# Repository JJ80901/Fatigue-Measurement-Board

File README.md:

# Fatigue-Measurement-Board
**Precision Displacement Sensing**

This board is designed to process and digitize a ±10V analog signal from a laser displacement sensor, ensuring high-fidelity data acquisition for fatigue testing applications. 

The signal enters through a BNC connector, passes through ESD protection and an RF filter, and is then scaled down to a ±1.65V range using a resistor divider. A non-inverting summing amplifier shifts the signal into a 0-3.3V range, with a 1.65V bias generated by an op-amp follower from a half-resistor divider off the 3.3V power rail.

To prevent aliasing, the conditioned signal passes through a third-order Butterworth Sallen-Key low-pass filter with a 5kHz cutoff frequency, optimized for sampling rates up to 1kHz. The filtered signal is digitized by an ADC141S626 14-bit ADC, which interfaces over SPI with an STM32F103CBT6 microcontroller, responsible for managing data acquisition and transmission.

Power is regulated using a TLV62569 switching regulator for 3.3V conversion and an HT7533-1 LDO, ensuring clean and stable power for the analog front end and microcontroller. 

This design improves upon earlier iterations by incorporating better filtering, precise voltage scaling, and a high-resolution ADC, making it ideal for fatigue analysis, precision displacement measurement, and other high-accuracy signal acquisition applications.

---

### What you'll find in this repository:
- Hardware designs (made in KiCad)
- STM32 Application Notes
- Device datasheets
- Circuit simulations

---

### Repository Project Structure:
- *3D Models* - Models for PCB components not found in the standard KiCad library
- *BOM* - An interactive HTML bill of materials (generated from the *Interactive HTML BOM* Plugin)
- *Datasheets* - Datasheets for specific devices used, such as the buck converter, LDO, Op-Amp, etc.
- *Docs* - STM32 application notes for crystal and USB design
- *Fatigue Test Board* - KiCad design files
- *Images* - High quality renderings of the final PCB in 3D
- *Libraries* - Folders to include schematic symbols and footprints for components not found in the standard KiCad library
- *Outputs* - Gerber files for manufacturing the PCB
- *Schematics* - PDFs of entire PCB schematic
- *Simulations* - LTSpice simulation block with any custom component libraries

---
***Disclaimer**: This board is ordered, but not yet tested!*

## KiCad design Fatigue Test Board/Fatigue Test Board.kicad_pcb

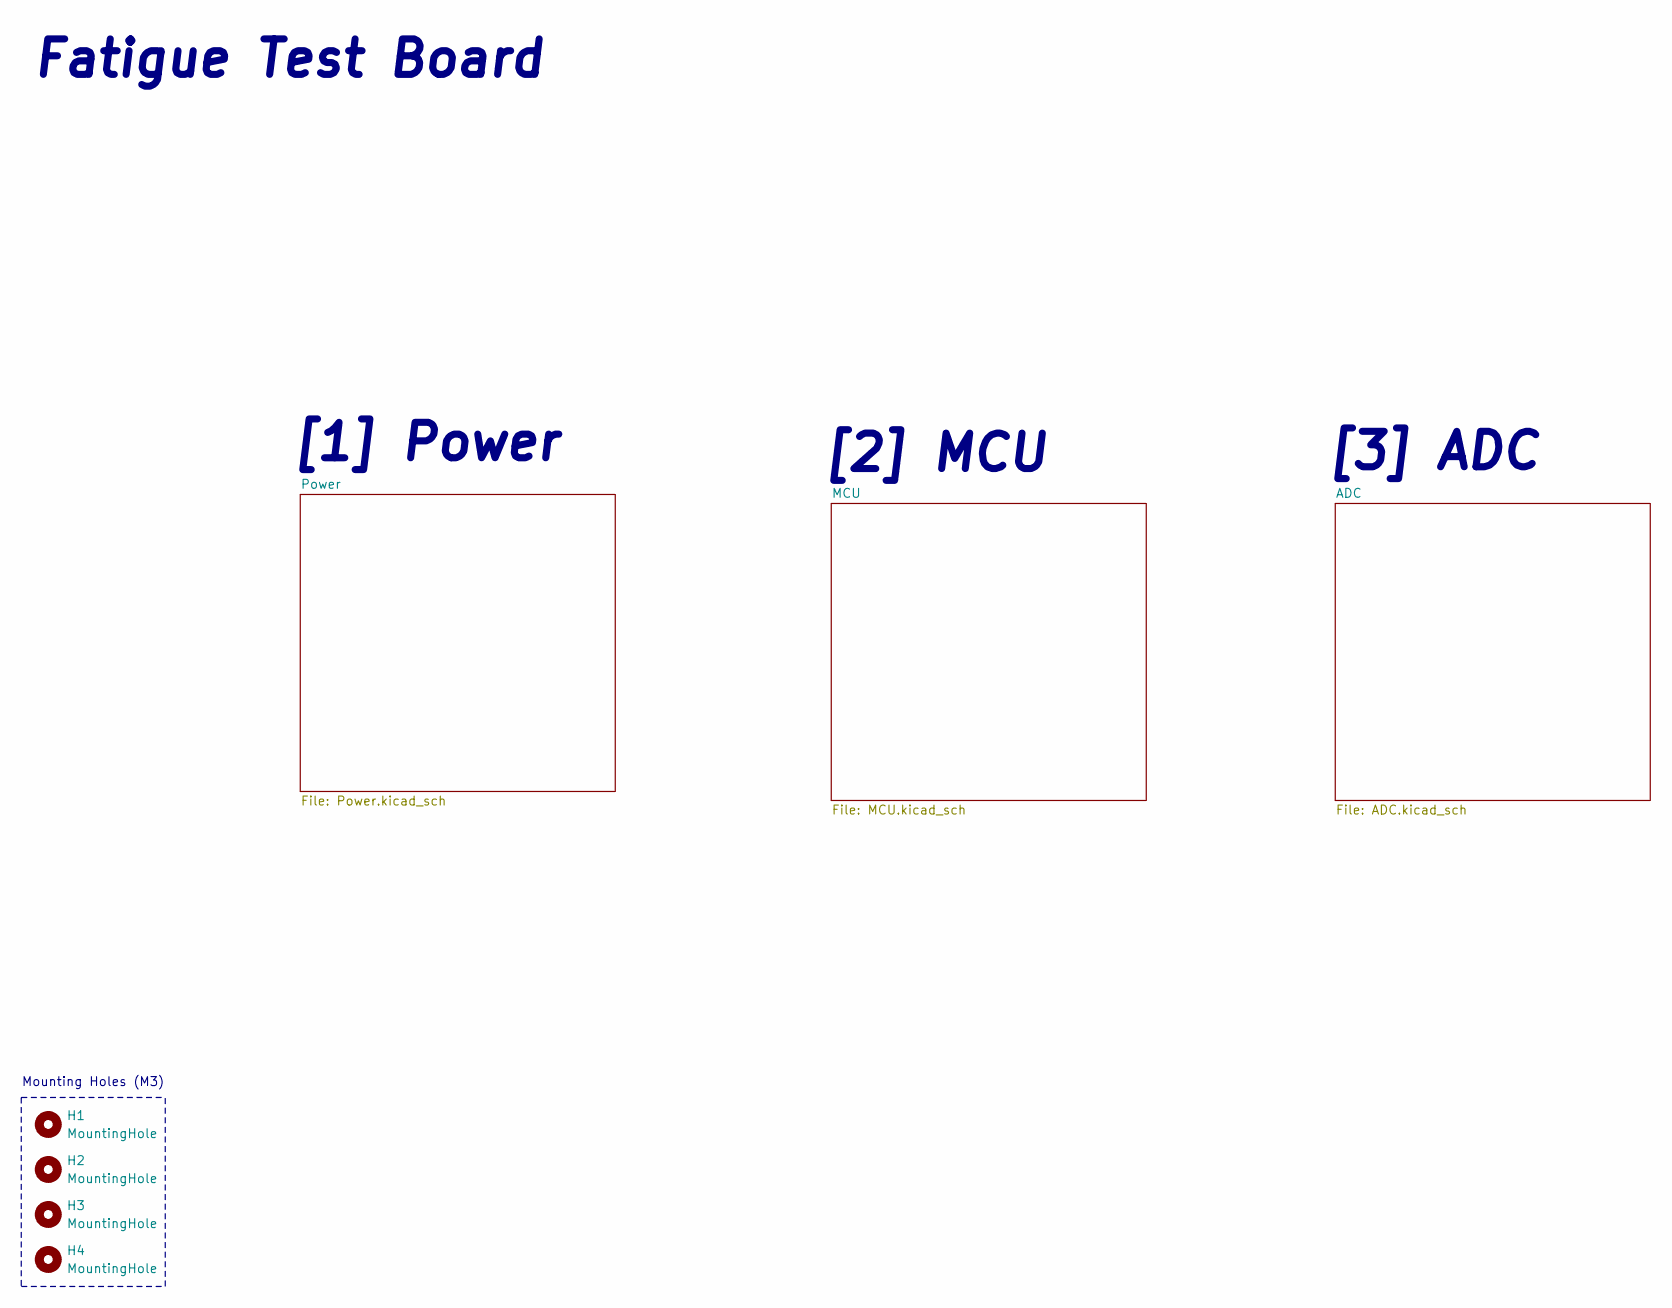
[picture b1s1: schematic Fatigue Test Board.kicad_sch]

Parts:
H1, H2, H3, H4: MountingHole; MountingHole_3.2mm_M3

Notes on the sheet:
[2] MCU
[3] ADC
Fatigue Test Board
[1] Power
Mounting Holes (M3)

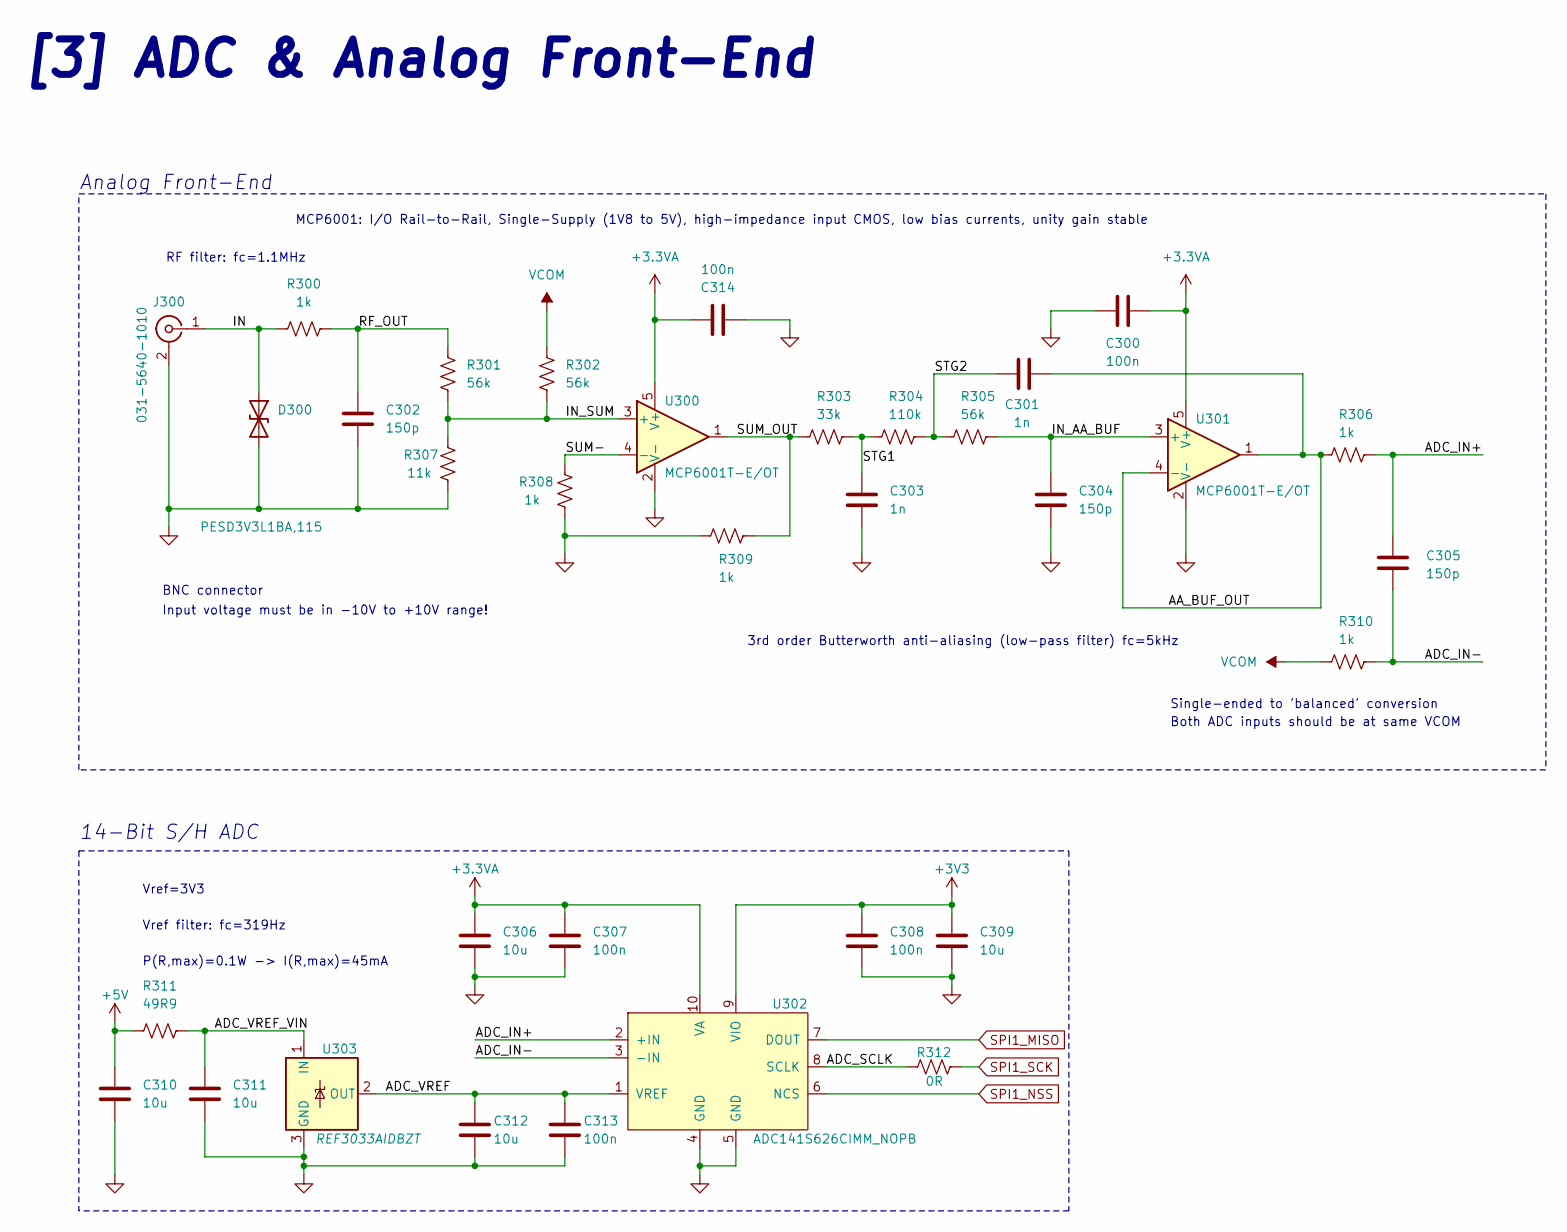
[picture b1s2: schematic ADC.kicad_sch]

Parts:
C300, C307, C308, C313, C314: 100n; C_0603_1608Metric_Pad1.08x0.95mm_HandSolder
C301, C303: 1n; C_0402_1005Metric_Pad0.74x0.62mm_HandSolder
C302, C304, C305: 150p; C_0402_1005Metric_Pad0.74x0.62mm_HandSolder
C306, C309, C310, C311, C312: 10u; C_0603_1608Metric_Pad1.08x0.95mm_HandSolder
D300: PESD3V3L1BA,115; D_SOD-323
J300: 031-5640-1010; CONN_73138-5033_MOL
R300, R306, R308, R309, R310: 1k; R_0603_1608Metric_Pad0.98x0.95mm_HandSolder
R301, R302, R305: 56k; R_0603_1608Metric_Pad0.98x0.95mm_HandSolder
R303: 33k; R_0603_1608Metric_Pad0.98x0.95mm_HandSolder
R304: 110k; R_0603_1608Metric_Pad0.98x0.95mm_HandSolder
R307: 11k; R_0603_1608Metric_Pad0.98x0.95mm_HandSolder
R311: 49R9; R_0603_1608Metric_Pad0.98x0.95mm_HandSolder
R312: 0R; R_0603_1608Metric_Pad0.98x0.95mm_HandSolder
U300, U301: MCP6001T-E/OT; SOT-23-5
U302: ADC141S626CIMM_NOPB; SOP50P490X110-10N
U303: REF3033AIDBZT; SOT-23

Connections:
+3.3VA: C300.1, C306.1, C307.1, C314.1, U300.5 (V+), U301.5 (V+), U302.10 (VA); also elsewhere on the board
+3V3: C308.1, C309.1, U302.9 (VIO); also elsewhere on the board
+5V: C310.1, R311.1; also elsewhere on the board
/ADC/AA_BUF_OUT: C301.2, R306.2, U301.1, U301.4 (-)
/ADC/ADC_IN+: C305.1, R306.1, U302.2 (+IN)
/ADC/ADC_IN-: C305.2, R310.1, U302.3 (-IN)
/ADC/ADC_SCLK: R312.2, U302.8 (SCLK)
/ADC/ADC_VREF: C312.1, C313.1, U302.1 (VREF), U303.2 (OUT)
/ADC/ADC_VREF_VIN: C311.1, R311.2, U303.1 (IN)
/ADC/IN: D300.1 (A1), J300.1 (In), R300.1
/ADC/IN_AA_BUF: C304.1, R305.1, U301.3 (+)
/ADC/IN_SUM: R301.2, R302.2, R307.1, U300.3 (+)
/ADC/RF_OUT: C302.1, R300.2, R301.1
/ADC/STG1: C303.1, R303.1, R304.2
/ADC/STG2: C301.1, R304.1, R305.2
/ADC/SUM-: R308.1, U300.4 (-)
/ADC/SUM_OUT: R303.2, R309.1, U300.1
GND: C300.2, C302.2, C303.2, C304.2, C306.2, C307.2, C308.2, C309.2, C310.2, C311.2, C312.2, C313.2, C314.2, D300.2 (A2), J300.2 (Ext), R307.2, R308.2, R309.2, U300.2 (V-), U301.2 (V-), U302.4 (GND), U302.5 (GND), U303.3 (GND); also elsewhere on the board
SPI1_MISO: U302.7 (DOUT); also elsewhere on the board
SPI1_NSS: U302.6 (NCS); also elsewhere on the board
SPI1_SCK: R312.1; also elsewhere on the board
VCOM: R302.1, R310.2; also elsewhere on the board

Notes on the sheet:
[3] ADC & Analog Front-End
RF filter: fc=1.1MHz
MCP6001: I/O Rail-to-Rail, Single-Supply (1V8 to 5V), high-impedance input CMOS, low bias currents, unity gain stable
3rd order Butterworth anti-aliasing (low-pass filter) fc=5kHz
P(R,max)=0.1W -> I(R,max)=45mA
Input voltage must be in -10V to +10V range!
Vref=3V3
Single-ended to 'balanced' conversion
Analog Front-End
Both ADC inputs should be at same VCOM
BNC connector
Vref filter: fc=319Hz
14-Bit S/H ADC

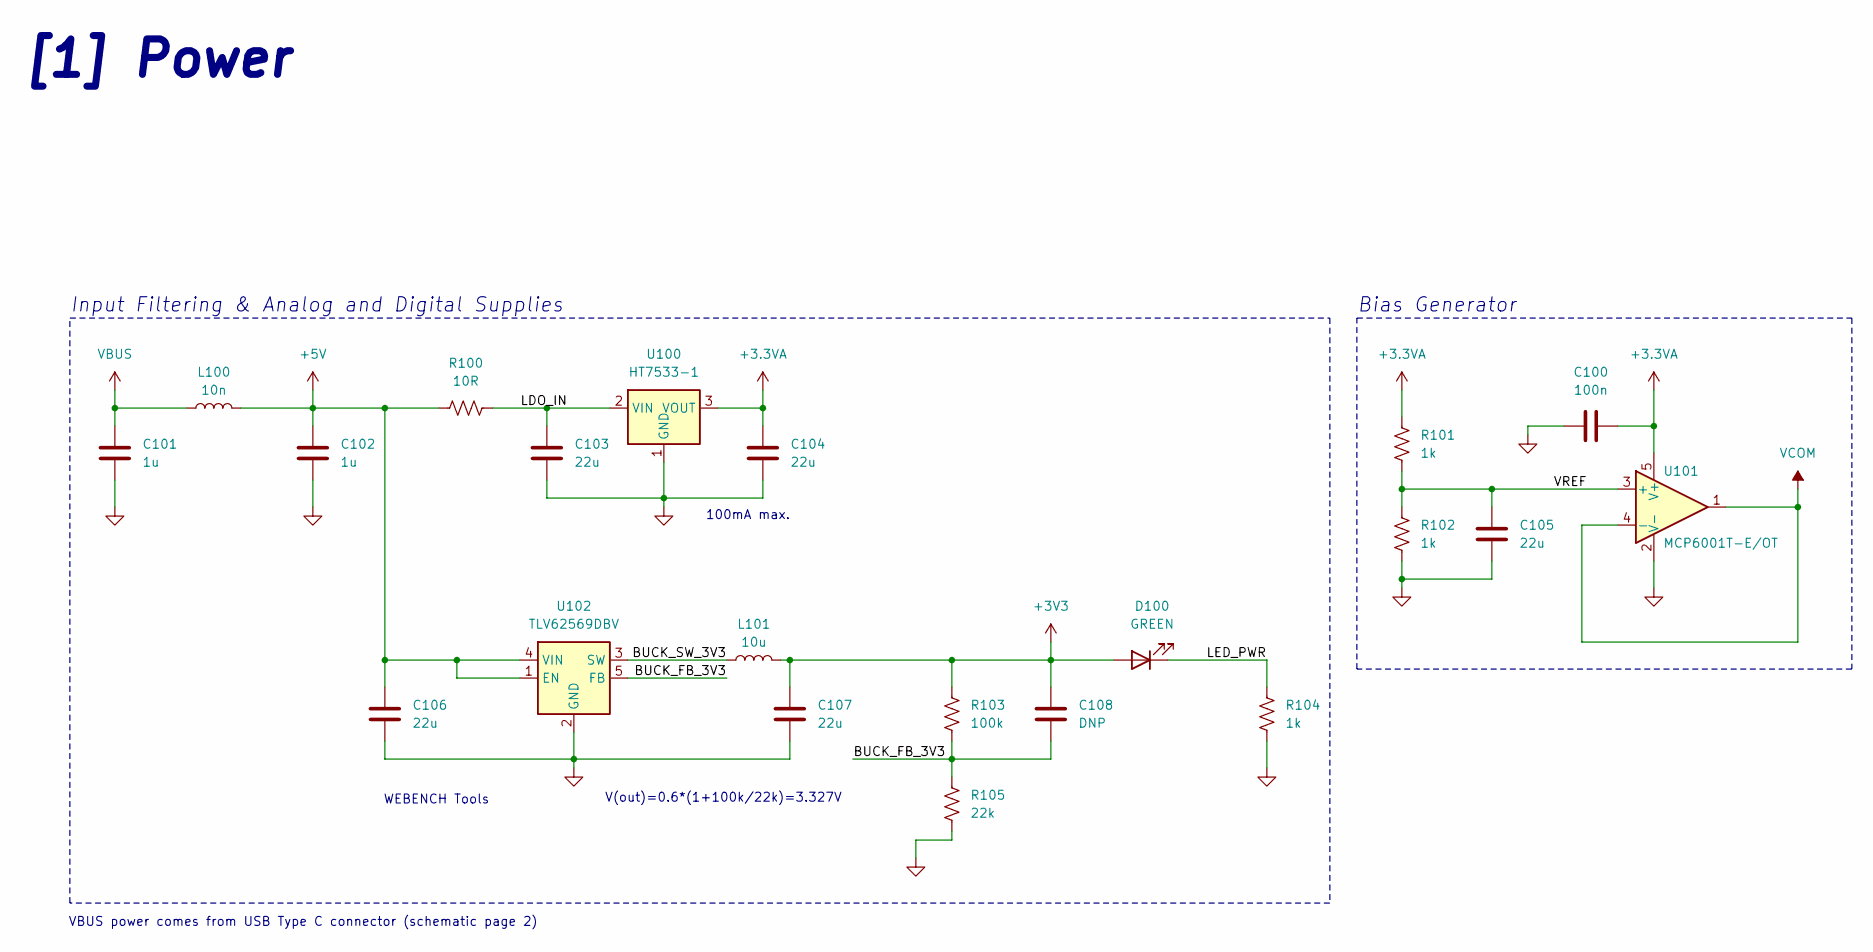
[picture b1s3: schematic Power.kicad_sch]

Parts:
C100: 100n; C_0603_1608Metric_Pad1.08x0.95mm_HandSolder
C101, C102: 1u; C_0603_1608Metric_Pad1.08x0.95mm_HandSolder
C103, C104, C105, C106, C107: 22u; C_0805_2012Metric_Pad1.18x1.45mm_HandSolder
C108: DNP; C_0603_1608Metric_Pad1.08x0.95mm_HandSolder
D100: GREEN; LED_0603_1608Metric_Pad1.05x0.95mm_HandSolder
L100: 10n; L_0603_1608Metric_Pad1.05x0.95mm_HandSolder
L101: 10u; IND_VLS4015CX-100M-H
R100: 10R; R_0603_1608Metric_Pad0.98x0.95mm_HandSolder
R101, R102, R104: 1k; R_0603_1608Metric_Pad0.98x0.95mm_HandSolder
R103: 100k; R_0603_1608Metric_Pad0.98x0.95mm_HandSolder
R105: 22k; R_0603_1608Metric_Pad0.98x0.95mm_HandSolder
U100: HT7533-1; SOT-89-3
U101: MCP6001T-E/OT; SOT-23-5
U102: TLV62569DBV; SOT-23-5

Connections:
+3.3VA: C100.2, C104.1, R101.2, U100.3 (VOUT), U101.5 (V+); also elsewhere on the board
+3V3: C107.1, C108.1, D100.2 (A), L101.2, R103.2; also elsewhere on the board
+5V: C102.1, C106.1, L100.2, R100.1, U102.1 (EN), U102.4 (VIN); also elsewhere on the board
/Power/BUCK_FB_3V3: C108.2, R103.1, R105.2, U102.5 (FB)
/Power/BUCK_SW_3V3: L101.1, U102.3 (SW)
/Power/LDO_IN: C103.1, R100.2, U100.2 (VIN)
/Power/LED_PWR: D100.1 (K), R104.2
/Power/VREF: C105.1, R101.1, R102.2, U101.3 (+)
GND: C100.1, C101.2, C102.2, C103.2, C104.2, C105.2, C106.2, C107.2, R102.1, R104.1, R105.1, U100.1 (GND), U101.2 (V-), U102.2 (GND); also elsewhere on the board
VBUS: C101.1, L100.1; also elsewhere on the board
VCOM: U101.1, U101.4 (-); also elsewhere on the board

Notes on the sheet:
V(out)=0.6*(1+100k/22k)=3.327V
Input Filtering & Analog and Digital Supplies
VBUS power comes from USB Type C connector (schematic page 2)
Bias Generator
100mA max.
WEBENCH Tools
[1] Power

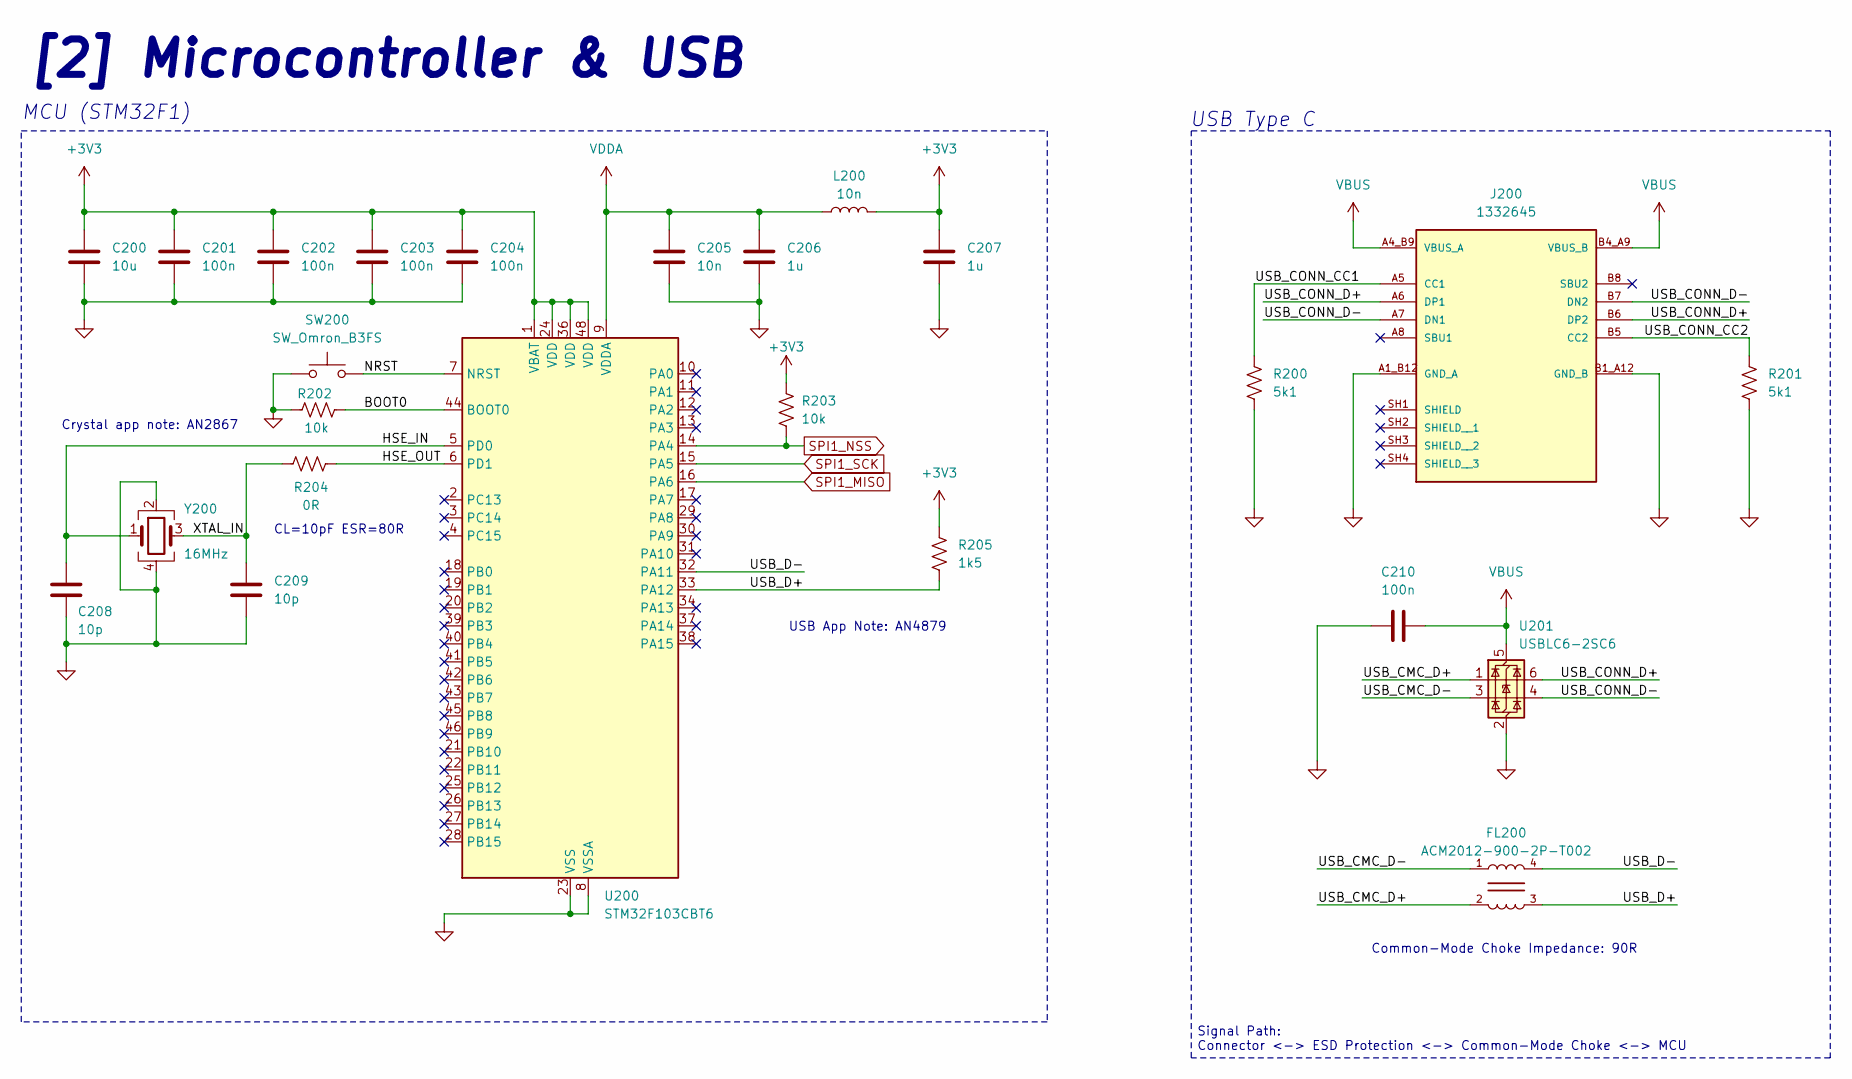
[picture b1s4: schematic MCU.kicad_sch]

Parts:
C200: 10u; C_0603_1608Metric_Pad1.08x0.95mm_HandSolder
C201, C202, C203, C204, C210: 100n; C_0603_1608Metric_Pad1.08x0.95mm_HandSolder
C205: 10n; C_0603_1608Metric_Pad1.08x0.95mm_HandSolder
C206, C207: 1u; C_0603_1608Metric_Pad1.08x0.95mm_HandSolder
C208, C209: 10p; C_0402_1005Metric_Pad0.74x0.62mm_HandSolder
FL200: ACM2012-900-2P-T002; FIL_ACM2012-900-2P-T002
J200: 1332645; PHOENIX_1332645; PARTREV 17.01.2022
L200: 10n; L_0603_1608Metric_Pad1.05x0.95mm_HandSolder
R200, R201: 5k1; R_0603_1608Metric_Pad0.98x0.95mm_HandSolder
R202, R203: 10k; R_0603_1608Metric_Pad0.98x0.95mm_HandSolder
R204: 0R; R_0603_1608Metric_Pad0.98x0.95mm_HandSolder
R205: 1k5; R_0603_1608Metric_Pad0.98x0.95mm_HandSolder
SW200: SW_Omron_B3FS; SW_PUSH_6mm
U200: STM32F103CBT6; LQFP-48_7x7mm_P0.5mm
U201: USBLC6-2SC6; SOT-23-6
Y200: 16MHz; Crystal_SMD_3225-4Pin_3.2x2.5mm

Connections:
+3V3: C200.1, C201.1, C202.1, C203.1, C204.1, C207.1, L200.2, R203.2, R205.1, U200.1 (VBAT), U200.24 (VDD), U200.36 (VDD), U200.48 (VDD); also elsewhere on the board
/MCU/BOOT0: R202.2, U200.44 (BOOT0)
/MCU/HSE_IN: C208.1, U200.5 (PD0), Y200.1
/MCU/HSE_OUT: R204.1, U200.6 (PD1)
/MCU/NRST: SW200.2, U200.7 (NRST)
/MCU/USB_CMC_D+: FL200.2, U201.1 (I/O1)
/MCU/USB_CMC_D-: FL200.1, U201.3 (I/O2)
/MCU/USB_CONN_CC1: J200.A5 (CC1), R200.1
/MCU/USB_CONN_CC2: J200.B5 (CC2), R201.1
/MCU/USB_CONN_D+: J200.A6 (DP1), J200.B6 (DP2), U201.6 (I/O1)
/MCU/USB_CONN_D-: J200.A7 (DN1), J200.B7 (DN2), U201.4 (I/O2)
/MCU/USB_D+: FL200.3, R205.2, U200.33 (PA12)
/MCU/USB_D-: FL200.4, U200.32 (PA11)
/MCU/XTAL_IN: C209.1, R204.2, Y200.3
GND: C200.2, C201.2, C202.2, C203.2, C204.2, C205.2, C206.2, C207.2, C208.2, C209.2, C210.2, J200.A1_B12 (GND_A), J200.B1_A12 (GND_B), R200.2, R201.2, R202.1, SW200.1, U200.8 (VSSA), U200.23 (VSS), U200.35 (VSS), U200.47 (VSS), U201.2 (GND), Y200.2, Y200.4; also elsewhere on the board
SPI1_MISO: U200.16 (PA6); also elsewhere on the board
SPI1_NSS: R203.1, U200.14 (PA4); also elsewhere on the board
SPI1_SCK: U200.15 (PA5); also elsewhere on the board
VBUS: C210.1, J200.A4_B9 (VBUS_A), J200.B4_A9 (VBUS_B), U201.5 (VBUS); also elsewhere on the board
VDDA: C205.1, C206.1, L200.1, U200.9 (VDDA)

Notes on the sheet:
Common-Mode Choke Impedance: 90R
CL=10pF ESR=80R
USB Type C
Signal Path: Connector <-> ESD Protection <-> Common-Mode Choke <-> MCU
Crystal app note: AN2867
[2] Microcontroller & USB
USB App Note: AN4879
MCU (STM32F1)

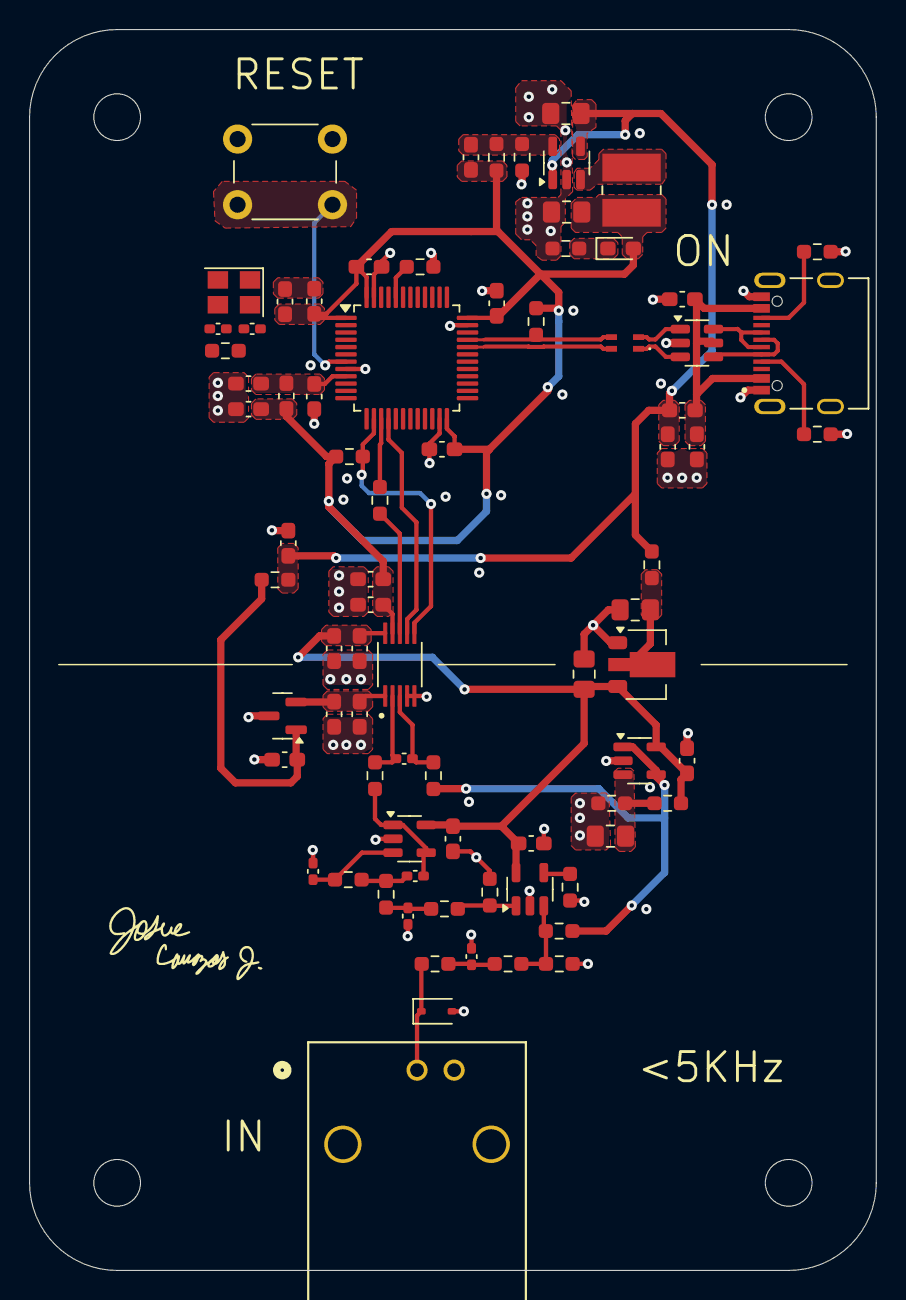
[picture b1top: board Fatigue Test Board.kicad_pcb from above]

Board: 4 copper layers, 58.0 x 85.0 mm, 83 parts (0 on the bottom side), 42 nets.

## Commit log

2025-02-25 Got rid of unwanted files
